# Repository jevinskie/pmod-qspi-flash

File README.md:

# pmod-qspi-flash
Simple Pmod PCB with a QSPI flash (targeted at PS4 reverse engineering tool development)

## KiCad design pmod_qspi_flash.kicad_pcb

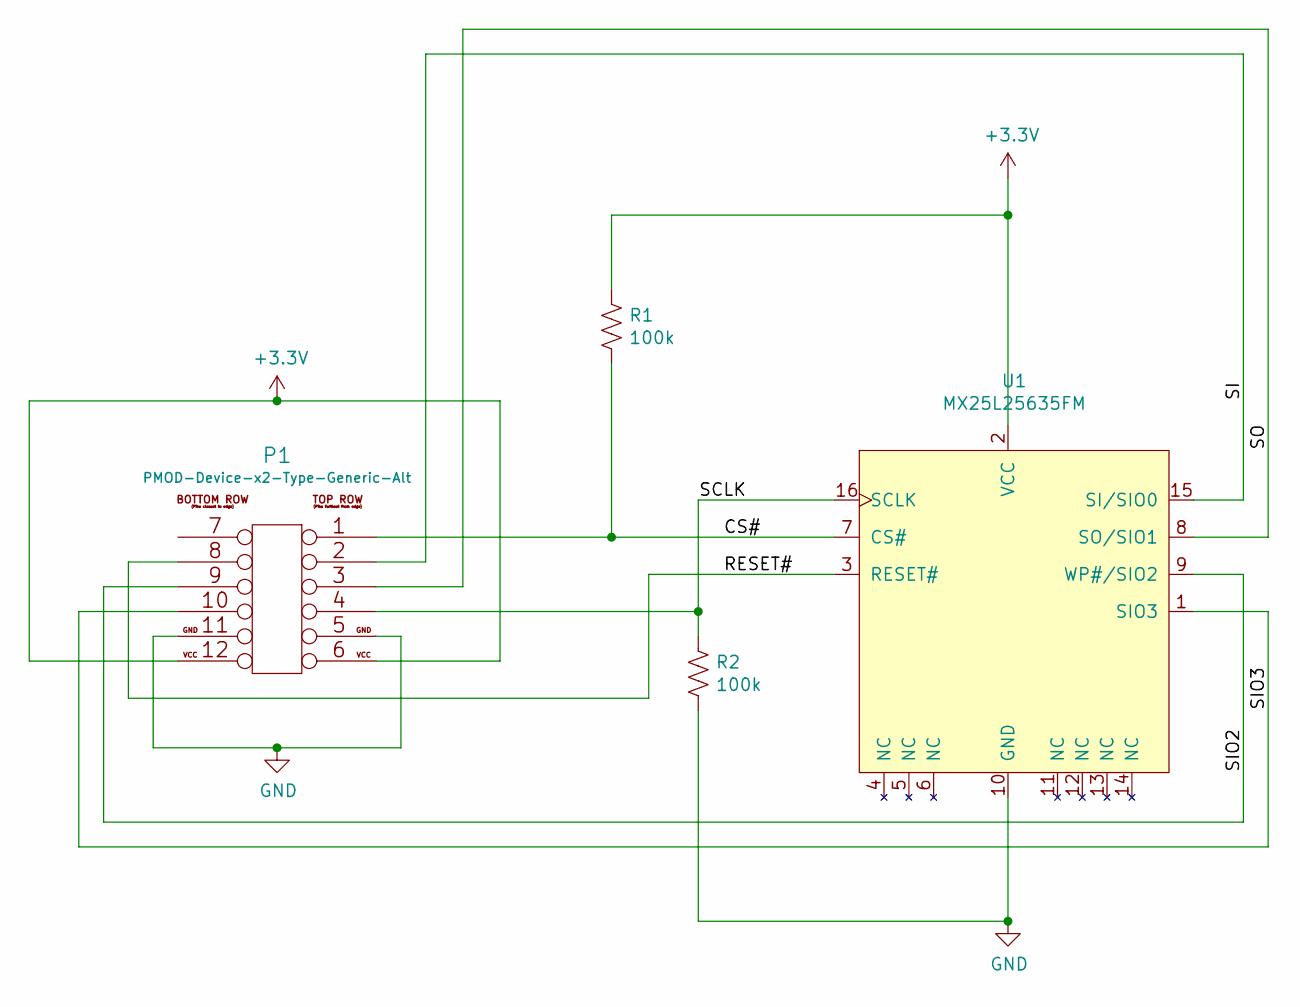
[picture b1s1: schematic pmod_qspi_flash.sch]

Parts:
P1: PMOD-Device-x2-Type-Generic-Alt; pmod_pin_array_6x2
R1, R2: 100k; R_1206_3216Metric_Pad1.30x1.75mm_HandSolder
U1: MX25L25635FM; SOIC-16W_7.5x10.3mm_P1.27mm

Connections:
+3V3: P1.6, P1.12, R1.1, U1.2 (VCC)
/CS#: P1.1, R1.2, U1.7 (CS#)
/RESET#: P1.8, U1.3 (RESET#)
/SCLK: P1.4, R2.1, U1.16 (SCLK)
/SI: P1.2, U1.15 (SI/SIO0)
/SIO2: P1.9, U1.9 (WP#/SIO2)
/SIO3: P1.10, U1.1 (SIO3)
/SO: P1.3, U1.8 (SO/SIO1)
GND: P1.5, P1.11, R2.2, U1.10 (GND)

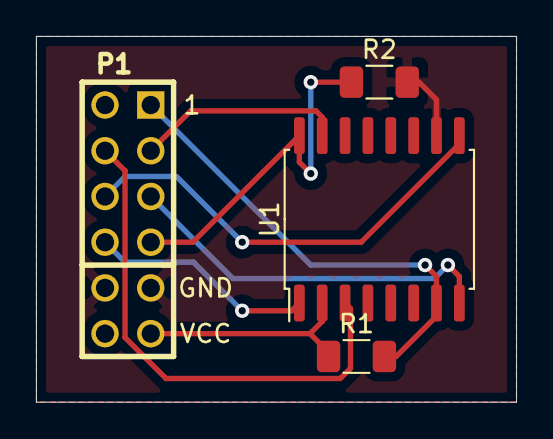
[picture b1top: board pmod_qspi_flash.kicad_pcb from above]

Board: 2 copper layers, 26.7 x 20.3 mm, 4 parts (0 on the bottom side), 9 nets.

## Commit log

2021-09-05 blank pcb/schematic
2021-09-05 add pmod library
2021-09-05 add qspi flash symbol and footprint
2021-09-06 routed but ugly, need to rotate flash to align with signals
2021-09-08 rotate qspi flash, shorter traces
2022-02-15 Create LICENSE
2022-02-16 add render
